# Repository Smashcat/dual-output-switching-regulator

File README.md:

# dual-output-switching-regulator
Small board with single 8-26v input and 5V@1.7A + 3.3V@500mA dual output via switching regulator

This board uses the cheap BD93291EFJ switching buck regulator which offers dual output, and is much more efficient than using linear regulators, while also allowing for higher input voltages than typical linear regulators; up to 26V. The board is very small - just 21mm x 30mm, so you can have 20 made at JLCPCB for under $1 :) Pin pitches are all quite large for surface mount, so a stencil isn't necessary to solder this board.

The pin headers are 2.54mm pitch, as the board is designed to be plugged into a breadboard as a convenient dual-rail power supply.

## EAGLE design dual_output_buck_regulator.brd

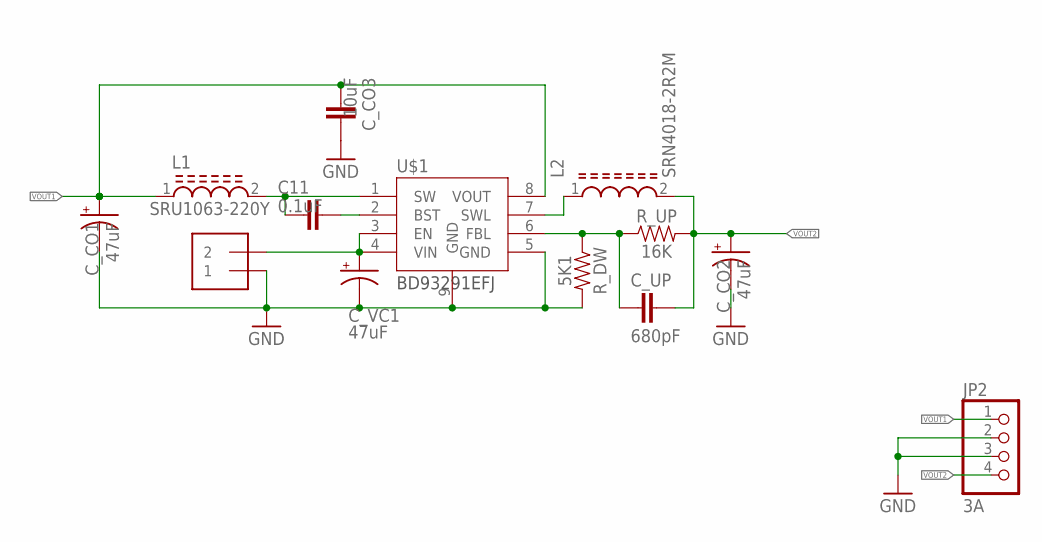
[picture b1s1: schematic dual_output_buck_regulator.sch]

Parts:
C11: 0.1uF; 0603
C_CO1, C_CO2: 47uF; PANASONIC_C
C_CO3: 10uF; 0603
C_UP: 680pF; 0603
C_VC1: 47uF; PANASONIC_C
J1: 1X2-3.5MM
JP2: 3A; 1X04
L1: SRU1063-220Y; IND_SRU1063-220Y
L2: SRN4018-2R2M; INDP4040X180N
R_DW: 5K1; 0603
R_UP: 16K; 0603
U$1: BD93291EFJ; SOIC127P600X100-9N

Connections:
GND: C_CO1.-, C_CO2.-, C_CO3.1, C_VC1.-, J1.1, JP2.2, JP2.3, R_DW.2, U$1.5 (GND), U$1.9 (GND)
unnamed: C_VC1.+, J1.2, U$1.3 (EN), U$1.4 (VIN)
unnamed: C11.1, U$1.2 (BST)
unnamed: C11.2, L1.2, U$1.1 (SW)
unnamed: C_UP.2, R_DW.1, R_UP.1, U$1.6 (FBL)
unnamed: L2.1, U$1.7 (SWL)
VOUT1: C_CO1.+, C_CO3.2, JP2.1, L1.1, U$1.8 (VOUT)
VOUT2: C_CO2.+, C_UP.1, JP2.4, L2.2, R_UP.2

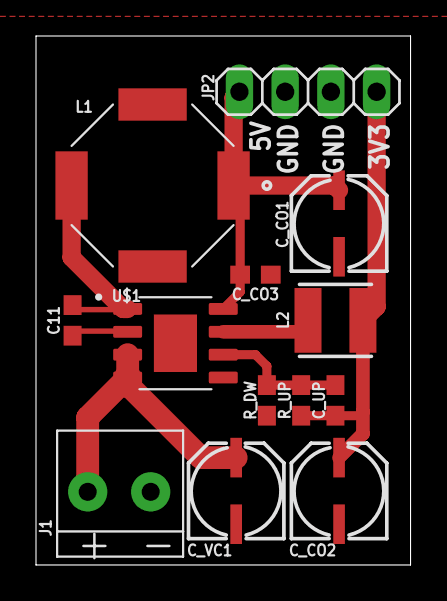
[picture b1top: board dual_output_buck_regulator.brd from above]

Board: 2 copper layers, 20.8 x 29.4 mm, 13 parts (0 on the bottom side), 8 nets.

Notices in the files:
parts and their libraries:
SparkFun-Capacitors: Licensing: Creative Commons ShareAlike 4.0 International - https://creativecommons.org/licenses/by-sa/4.0
